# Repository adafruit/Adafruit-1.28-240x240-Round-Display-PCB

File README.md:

## Adafruit 1.28 240x240 Round Display with MicroSD - GC9A01A with EYESPI Connector PCB

<a href="http://www.adafruit.com/products/6178"><br/>
Click here to purchase one from the Adafruit shop</a>

PCB files for the Adafruit 1.28 240x240 Round Display with MicroSD - GC9A01A with EYESPI Connector. 

Format is EagleCAD schematic and board layout
* https://www.adafruit.com/product/6178

### Description

'Round these parts we enjoy unusually-shaped displays. And this one certainly fits the description - it's a 1.28" diagonal TFT that comes in a round shape and contains a high density 220 ppi, 240x240 pixel RGB display with full-angle viewing. It looks a lot like our 1.54" 240x240 squar display, but with the edges beveled off.  We've seen displays like this often used in smartwatches and small electronic devices but they've always been MIPI interface. Finally, we found one that is SPI and has a friendly display driver, so it works with any and all microcontrollers or microcomputers!

This lovely little display breakout is the best way to add a small, round, colorful and very bright display to any project. Since the display uses 4-wire SPI to communicate and has its own pixel-addressable frame buffer, it can be used with every kind of microcontroller. Even a very small one with low memory and few pins available! The 1.28" display has 240x240 16-bit full color pixels and is an IPS display, so the color looks great up to 80 degrees off axis in any direction. The TFT driver (GC9A01A) is very similar to the popular ST7789, and our Arduino library supports it well.

The breakout has the TFT display soldered on (it uses a delicate flex-circuit connector) as well as an ultra-low-dropout 3.3V regulator, auto-reset circuitry, and a 3/5V level shifter so you can use it with 3.3V or 5V power and logic. We also had a little extra space, so we placed a microSD card holder so you can easily load full color bitmaps from a FAT16/FAT32 formatted microSD card. The microSD card is not included, but you can pick one up here.

Of course, we wouldn't just leave you with a datasheet and a "good luck!" - we've written a full open-source graphics Arduino library that can draw pixels, lines, rectangles, circles, text, and bitmaps as well as example code. The code is written for Arduino but can be easily ported to your favorite microcontroller! Wiring is easy, we strongly encourage using the hardware SPI pins of your Arduino as software SPI is noticeably slower when dealing with this size display. For Raspberry Pi or other Single Board Computer Python users, we have a user-space Pillow-compatible library. For CircuitPython there's a contributed displayio driver for native support.

This display breakout also features a 18-pin "EYESPI" standard FPC connector with flip-top connector. You can use a 18-pin 0.5mm pitch FPC cable (not included!) to connect to all the GPIO pins, for when you want to skip the soldering.

### License

Adafruit invests time and resources providing this open source design, please support Adafruit and open-source hardware by purchasing products from [Adafruit](https://www.adafruit.com)!

Designed by Limor Fried/Ladyada for Adafruit Industries.

Creative Commons Attribution/Share-Alike, all text above must be included in any redistribution. 
See license.txt for additional details.

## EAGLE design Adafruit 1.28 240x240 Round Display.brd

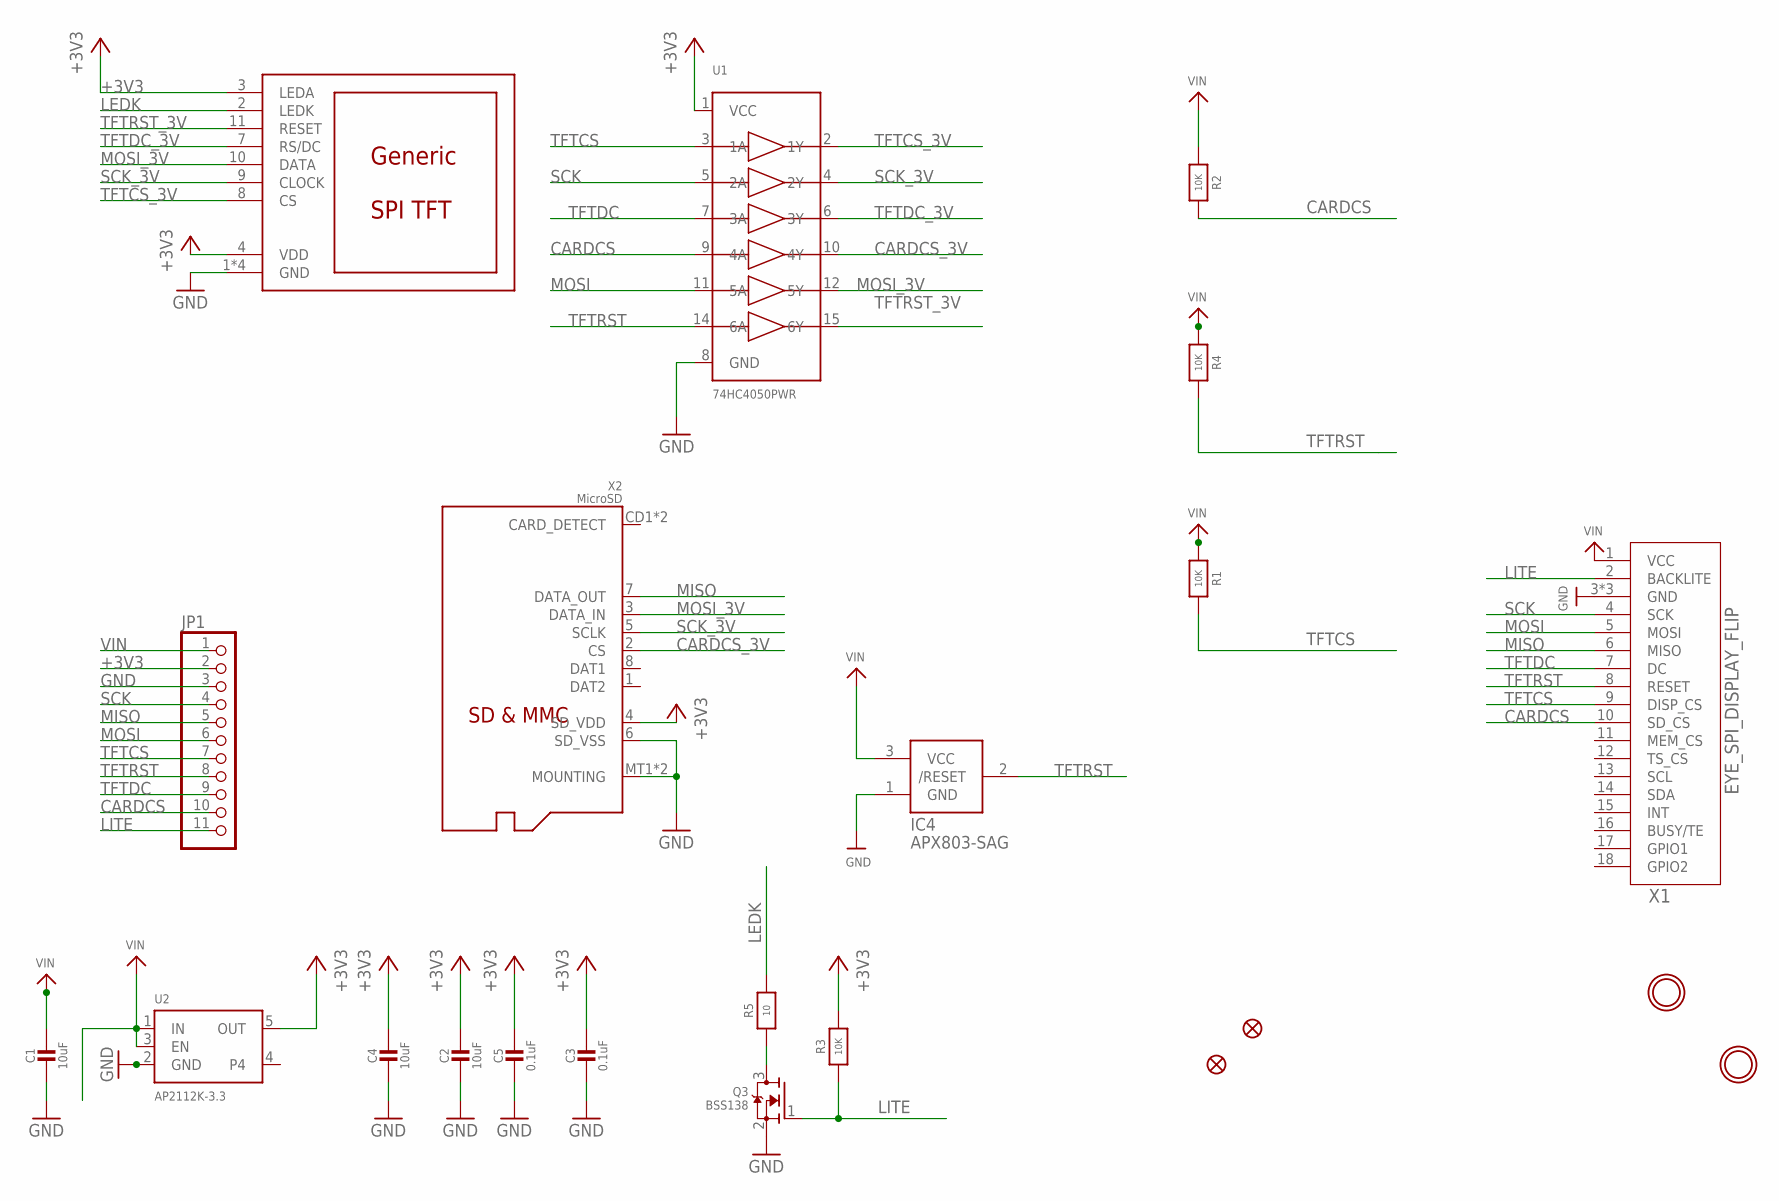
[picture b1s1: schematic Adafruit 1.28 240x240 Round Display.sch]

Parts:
C1, C2, C4: 10uF; 0805-NO
C3, C5: 0.1uF; 0603-NO
DISP1: DISP_LCD_GENERIC_SPI_1.28_240X240_ROUND; TFT_1.28IN_ROUND_240X240_12P
IC4: APX803-SAG; SOT23-WIDE
JP1: HEADER-1X1176MIL; 1X11_ROUND_76
Q3: BSS138; SOT23-WIDE
R1, R2, R3, R4: 10K; 0603-NO
R5: 10; 0603-NO
U1: 74HC4050PWR; TSSOP16
U2: AP2112K-3.3; SOT23-5; JLC_ROTATION 0
U$4, U$5: FIDUCIAL_1MM
U$9, U$10: MOUNTINGHOLE2.5; MOUNTINGHOLE_2.5_PLATED
X1: EYE_SPI_DISPLAY_FLIP; EYE_SPI_DISPLAY_BOTCONTACT
X2: MicroSD; MICROSD

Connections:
+3V3: C2.1, C3.1, C4.1, C5.1, DISP1.3 (LEDA), DISP1.4 (VDD), JP1.2, R3.2, U1.1 (VCC), U2.5 (OUT), X2.4 (SD_VDD)
CARDCS: JP1.10, R2.1, U1.9 (4A), X1.10 (SD_CS)
CARDCS_3V: U1.10 (4Y), X2.2 (CS)
GND: C1.2, C2.2, C3.2, C4.2, C5.2, DISP1.1 (GND), DISP1.5 (GND), DISP1.6 (GND), DISP1.12 (GND), IC4.1 (GND), JP1.3, Q3.2 (S), U1.8 (GND), U2.2 (GND), X1.3 (GND), X1.SUPPORT1 (GND), X1.SUPPORT2 (GND), X2.6 (SD_VSS), X2.MT1 (MOUNTING), X2.MT2 (MOUNTING)
LEDK: DISP1.2 (LEDK), R5.2
LITE: JP1.11, Q3.1 (G), R3.1, X1.2 (BACKLITE)
MISO: JP1.5, X1.6 (MISO), X2.7 (DATA_OUT)
MOSI: JP1.6, U1.11 (5A), X1.5 (MOSI)
MOSI_3V: DISP1.10 (DATA), U1.12 (5Y), X2.3 (DATA_IN)
unnamed: Q3.3 (D), R5.1
SCK: JP1.4, U1.5 (2A), X1.4 (SCK)
SCK_3V: DISP1.9 (CLOCK), U1.4 (2Y), X2.5 (SCLK)
TFTCS: JP1.7, R1.1, U1.3 (1A), X1.9 (DISP_CS)
TFTCS_3V: DISP1.8 (CS), U1.2 (1Y)
TFTDC: JP1.9, U1.7 (3A), X1.7 (DC)
TFTDC_3V: DISP1.7 (RS/DC), U1.6 (3Y)
TFTRST: IC4.2 (/RESET), JP1.8, R4.1, U1.14 (6A), X1.8 (RESET)
TFTRST_3V: DISP1.11 (RESET), U1.15 (6Y)
VIN: C1.1, IC4.3 (VCC), JP1.1, R1.2, R2.2, R4.2, U2.1 (IN), U2.3 (EN), X1.1 (VCC)

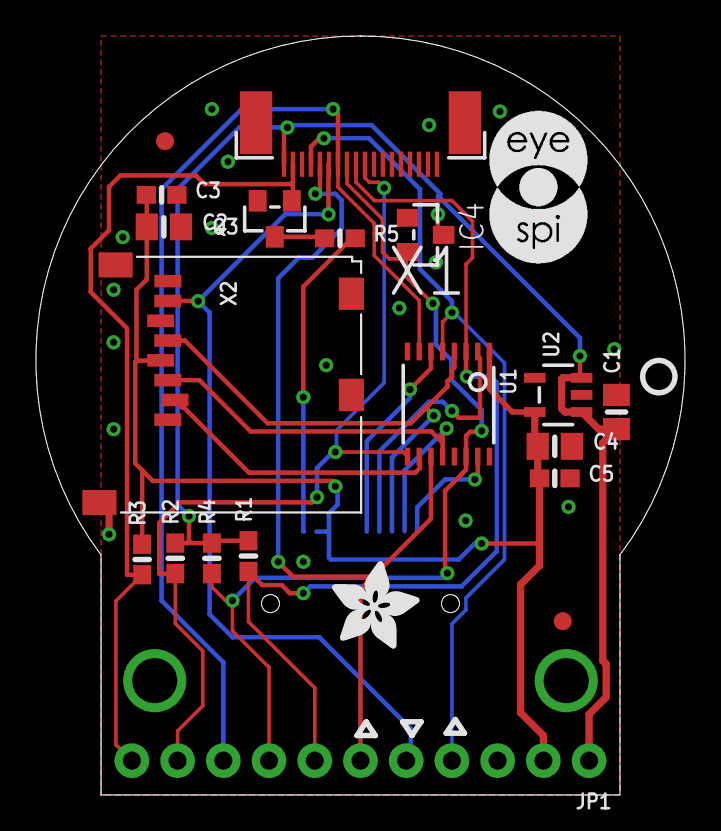
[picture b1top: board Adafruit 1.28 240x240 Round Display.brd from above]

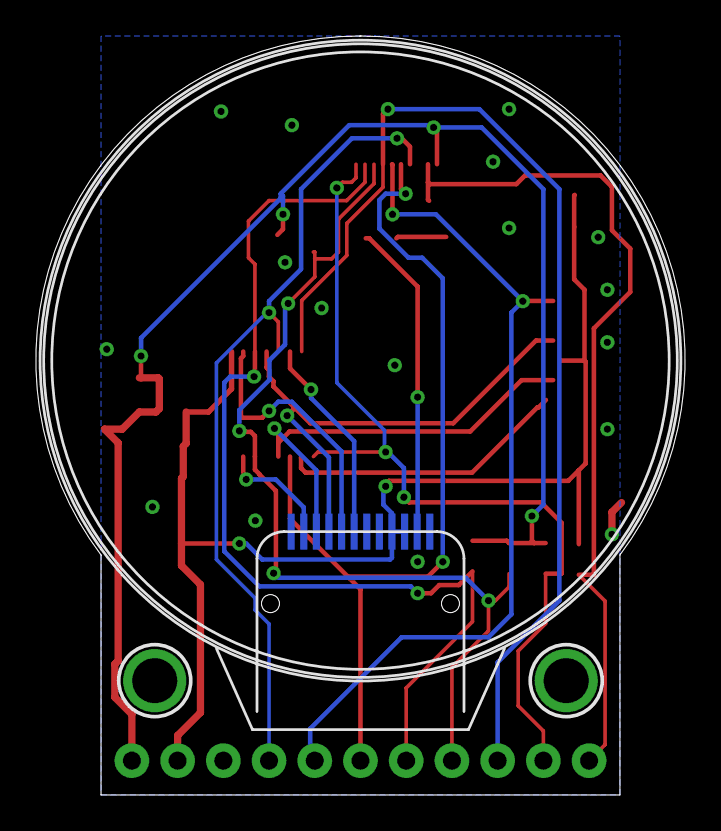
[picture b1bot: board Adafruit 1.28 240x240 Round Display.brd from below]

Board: 2 copper layers, 36.1 x 42.2 mm, 45 parts (9 on the bottom side), 19 nets.

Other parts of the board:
PLABEL0: PLABEL0
PLABEL1: PLABEL1
PLABEL2: PLABEL2
PLABEL3: PLABEL3
PLABEL4: PLABEL4
PLABEL5: PLABEL5
PLABEL6: PLABEL6
PLABEL7: PLABEL7
PLABEL8: PLABEL8
PLABEL13: PLABEL13
PLABEL14: PLABEL14
PLABEL15: PLABEL15
PLABEL16: PLABEL16
PLABEL17: PLABEL17
PLABEL23: PLABEL23
PLABEL24: PLABEL24
PLABEL25: PLABEL25
PLABEL26: PLABEL26
PLABEL27: PLABEL27
PLABEL28: PLABEL28
U$1: ADAFRUIT_5MM
U$2: PCBFEAT-REV-040
U$7: EYESPI_MINI_LOGO

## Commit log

2025-02-07 cookiecutter

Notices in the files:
parts and their libraries:
microbuilder: This work is placed in the public domain, and may be freely used for commercial and non-commercial work with the following conditions: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
